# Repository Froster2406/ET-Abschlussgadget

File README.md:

# HS20-23 ET Abschlussgadget

Als Teil der Abschlusszeitung gibt es auch dieses Jahr wieder ein kleines Gadget kostenfrei dazu. Ganz im Namen des Überthemas "ET im PRENpunkt" mit der Anlehung an "Familien im Brennpunkt", kannst auch Du herausfinden, wie viel ET in Dir steckt. Aber nur wenn Du so asozial wie ein ET'ler bist, schaltet sich die geheime Zusatzfunktion frei.

## Verwendung

* Beiligende Batterie einlegen
* Schalter auf Platine in ON-Zustand versetzten
* Finger auf "Drück mich!" legen
* Anzeige ablesen

<details>
<summary>only for real engineers</summary>
<br>
You deem yourself a true engineer? Great!<br>
Tag along as we dive deeper into how you can reprogram the microcontroller. <br>

## general information
* [Reference Manual](https://ww1.microchip.com/downloads/aemDocuments/documents/MCU08/ProductDocuments/DataSheets/ATtiny212-214-412-414-416-DataSheet-DS40002287A.pdf)
* There are two pins (J1 & J2) on the side of the PCB than can be freely addressed, without interfering with the main functionality of the board

## preresquisites
* USB to serial converter | USB to TTL converter <br>
`Any converter (3.3V or 5V) off of Aliexpress, Ebay, Mouser, etc. will do.`
* 1kOhm resistor <br>
* Wires to connect the PCB to the converter <br>
* [Microchip Studio](https://www.microchip.com/en-us/tools-resources/develop/microchip-studio) <br>
* [Python](https://www.python.org/downloads/) installed on your machine <br>
* Python package: [pymcuprog](https://pypi.org/project/pymcuprog/) <br>
`pip install pymcuprog`<br>

## wiring diagram 
https://github.com/microchip-pic-avr-tools/pymcuprog#serial-port-updi-pyupdi

## reprogramming
* Connect the PCB to the USB to serial converter according to the wiring diagram
* Adjust the code to your liking and build it with F7
* Navigate to the python-programmer script <br>
`cd <YOUR_PATH>\ET-Abschlussgadget\Software\Programmer Python`
* Run the programming command <br>
`python attiny414.py <COM_PORT> <ABSOLUTE_PATH_TO_HEX_FILE_YOU_COMPILED_WITH_MICROCHIP_STUDIO>` <br>
*COM_PORT: If unknown, the available ones will be printed in the console*

* Power cycle the PCB

</details>

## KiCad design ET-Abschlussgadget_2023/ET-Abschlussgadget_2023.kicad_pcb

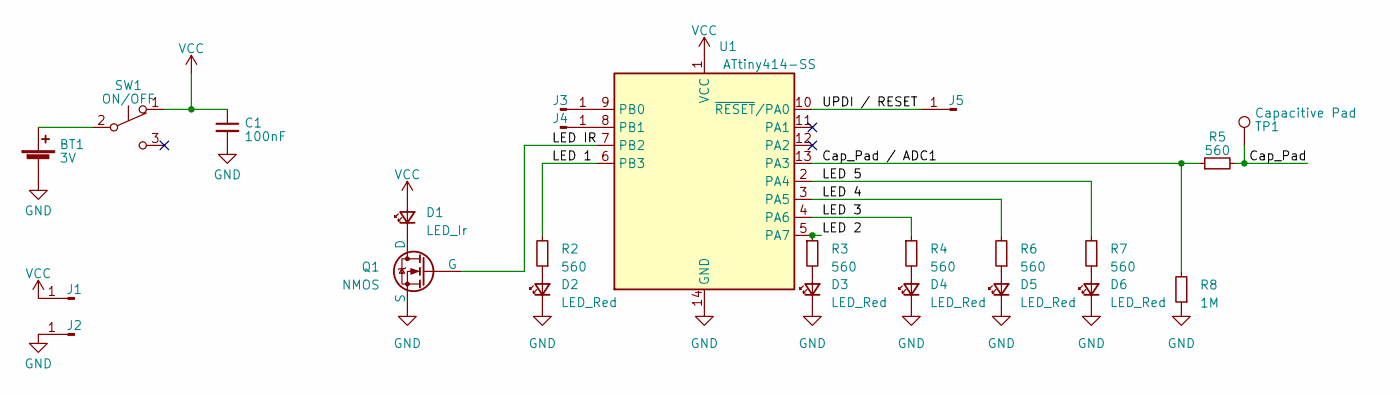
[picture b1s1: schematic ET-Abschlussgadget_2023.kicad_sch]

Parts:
BT1: 3V; BAT-SMD_CR2032-3V; LCSC C70373
C1: 100nF; C0603; LCSC C38141
D1: LED_Ir; XS-IR04A05-802; LCSC C396649
D2, D3, D4, D5, D6: LED_Red; LED0603-RD_RED; LCSC C965799
J1, J2: EXTCLK; TestPoint_Pad_D2.0mm
J3: PB0; TestPoint_Pad_D1.0mm
J4: PB1; TestPoint_Pad_D1.0mm
J5: UPDI / RESET; TestPoint_Pad_D2.0mm
Q1: NMOS; SOT-23-3_L2.9-W1.3-P1.90-LS2.4-BR
R2, R3, R4, R5, R6, R7: 560; R_0603_1608Metric_Pad0.98x0.95mm_HandSolder; LCSC C5140946
R8: 1M; R_0603_1608Metric_Pad0.98x0.95mm_HandSolder; LCSC C5140946
SW1: ON/OFF; SW-TH_MSK12C02; LCSC C2681568
TP1: Capacitive Pad; TestPoint_Pad_4.0x4.0mm
U1: ATtiny414-SS; SOIC-14_L8.7-W3.9-P1.27-LS6.0-BL; LCSC C189365

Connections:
/Cap_Pad: R5.2, TP1.1
/Cap_Pad / ADC1: R5.1, R8.2, U1.13 (PA3)
/LED 1: R2.2, U1.6 (PB3)
/LED 2: R3.1, U1.5 (PA7)
/LED 3: R4.1, U1.4 (PA6)
/LED 4: R6.2, U1.3 (PA5)
/LED 5: R7.2, U1.2 (PA4)
/LED IR: Q1.2 (G), U1.7 (PB2); also elsewhere on the board
/UPDI / RESET: J5.1, U1.10 (~RESET/PA0)
GND: BT1.2 (-), C1.2, D2.1 (K), D3.1 (K), D4.1 (K), D5.1 (K), D6.1 (K), J2.1, Q1.3 (S), R8.1, U1.14 (GND); also elsewhere on the board
unnamed: BT1.1 (+), SW1.2 (B)
unnamed 11: D1.1 (K), Q1.1 (D); also elsewhere on the board
unnamed: D2.2 (A), R2.1
unnamed: D3.2 (A), R3.2
unnamed: D4.2 (A), R4.2
unnamed: D5.2 (A), R6.1
unnamed: D6.2 (A), R7.1
unnamed: J3.1, U1.9 (PB0)
unnamed: J4.1, U1.8 (PB1)
VCC: C1.1, D1.2 (A), J1.1, SW1.1 (A), U1.1 (VCC)

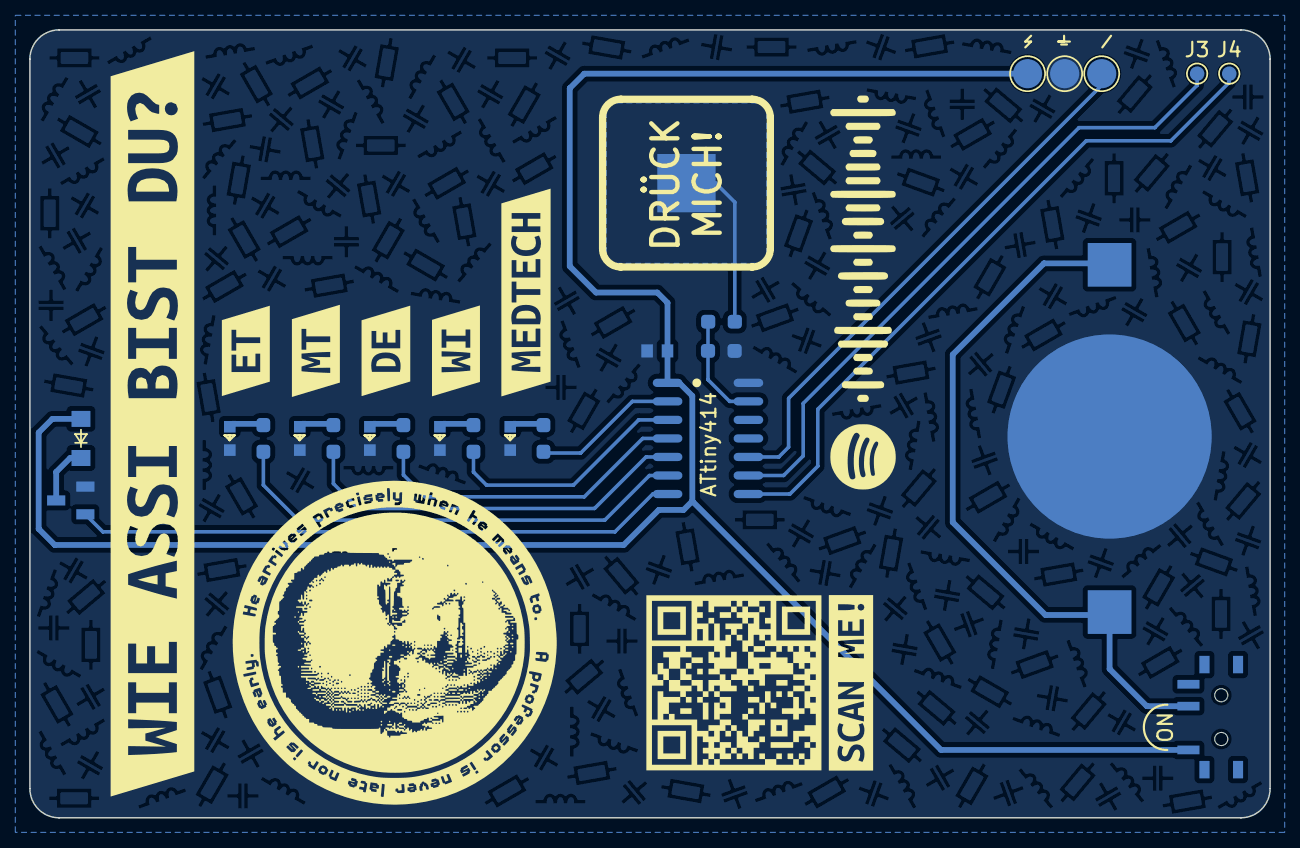
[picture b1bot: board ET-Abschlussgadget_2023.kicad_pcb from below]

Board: 2 copper layers, 85.0 x 54.0 mm, 31 parts (31 on the bottom side), 20 nets.

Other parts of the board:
Q2: SI2302_C2891732; SOT-23-3_L2.9-W1.3-P1.90-LS2.4-BR
kibuzzard-642F12C7: G***; kibuzzard-642F12C7
kibuzzard-642F12D5: G***; kibuzzard-642F12D5
kibuzzard-642F12E3: G***; kibuzzard-642F12E3
kibuzzard-642F12EF: G***; kibuzzard-642F12EF
kibuzzard-642F1274: G***; kibuzzard-642F1274
kibuzzard-642F1300: G***; kibuzzard-642F1300
kibuzzard-64480F6A: G***; kibuzzard-64480F6A

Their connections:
/LED IR: Q2.1 (G); also elsewhere on the board
GND: Q2.2 (S); also elsewhere on the board
unnamed 11: Q2.3 (D); also elsewhere on the board

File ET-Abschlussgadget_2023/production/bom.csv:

Designator,Footprint,Quantity,Value,LCSC Part #
BT1,BAT-SMD_CR2032-3V,1,3V,C70373
C1,C0603,1,100nF,C38141
D1,XS-IR04A05-802,1,LED_Ir,C396649
"D2, D3, D4, D5, D6",LED0603-RD_RED,5,LED_Red,C965799
"J1, J2",TestPoint_Pad_D2.0mm,2,EXTCLK,
J3,TestPoint_Pad_D1.0mm,1,PB0,
J4,TestPoint_Pad_D1.0mm,1,PB1,
J5,TestPoint_Pad_D2.0mm,1,UPDI / RESET,
Q2,SOT-23-3_L2.9-W1.3-P1.90-LS2.4-BR,1,SI2302_C2891732,C2891732
"R2, R3, R4, R5, R6, R7",0603,6,560,C5140946
R8,0603,1,1M,C5140946
SW1,SW-TH_MSK12C02,1,ON/OFF,C2681568
TP1,TestPoint_Pad_4.0x4.0mm,1,Capacitive Pad,
U1,SOIC-14_L8.7-W3.9-P1.27-LS6.0-BL,1,ATtiny414-SS,C189365

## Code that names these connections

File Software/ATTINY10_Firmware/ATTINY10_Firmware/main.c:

/*
                                         ATtiny10
                                 +----------------------+
        AIN0/ADC0/OC0A/PCINT0  --| 1 (PB0)  (PB3/RST) 6 |--  ADC3/PCINT3
                                 |                      |
                                 |                      |
                               --| 2 (GND)      (VCC) 5 |--
                                 |                      |
                                 |                      |
 AIN1/ADC1/OC0B/PCINT1/QTouch  --| 3 (PB1)      (PB2) 4 |--  ADC2/PCINT2
                                 +----------------------+

*/


#define F_CPU 8000000

#include <avr/io.h>
#include <util/delay.h>
#include "tiny_lib.h"
#include "TinyTouchLib.h"

uint8_t irCmd[] = {0x76, 0xB5, 0xAA, 0xB5, 0xAD};

int main(void)
{
	/*
	// Blink led on pin 1
	// -----------------------------
	// Pin 1 as output
    DDRB = 0b0001;
    // Toggle OC0A, CTC mode
	TCCR0A = 1<<COM0A0 | 0<<WGM00;
    // CTC mode; use OCR0A
	TCCR0B = 1<<WGM02 | 3<<CS00;
	// 1 second
	OCR0A = 15624;
	*/
	
	/*
	// IR led pwm signal
	// -----------------------------
	led6On();
	pwm1Init();
	pwm1On();
	_delay_us(560);
	pwm1Off();
	_delay_us(560);
	*/
	
	//tinytouch_init();
	
	/*
	DDRB = 1;                    // PB0 as an output
	TCCR0A = 1<<COM0A0;          // Toggle OC0A
	TCCR0B = 1<<WGM02 | 3<<CS00; // CTC mode and set prescaler to 64
	OCR0A = 3905;                // Frequency 2Hz
	while (1);
	*/
	
	
	CCP    = 0xD8;
	CLKMSR = 0x00;
	CCP    = 0xD8;
	CLKPSR = 0X00;
	
	/*
	DDRB = 0b1111;
	PUEB = 0b0000;
	PORTB = 0b0000;
	*/
	
	while (1) 
    {
		/*
		PORTB = 0b0001;
		_delay_ms(200);
		PORTB = 0b0100;
		_delay_ms(200);
		*/
		
		/*
		// Capacitive touch sensor
		// -----------------------------
		if (tinytouch_sense() == tt_push) {
			led1On();
			_delay_ms(200);
			ledsOff();
		}
		*/
		
		/*
		// Send ir command
		// -----------------------------
		for(uint8_t n = 0; n < 2; n++) {
			for (uint8_t i = 0; i < sizeof(irCmd)/sizeof(irCmd[0]); i++) {
				for (uint8_t j = 0; j < sizeof(irCmd[0]); j++) {
					if (irCmd[i] & (1 << (7 - j))) {
						led6On();
						_delay_us(625);
					}
					else {
						ledsOff();
						_delay_us(625);
					}
				}
			}
			_delay_ms(25);
		}
		*/
		
		#define DEL 100
		
		// Blink 6 charlieplexed leds
		// -----------------------------
		led1On();
		_delay_ms(DEL);
		led2On();
		_delay_ms(DEL);
		led3On();
		_delay_ms(DEL);
		led4On();
		_delay_ms(DEL);
		led5On();
		_delay_ms(DEL);
		led6On();
		_delay_ms(DEL);
    }
}

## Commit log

2023-03-31 V0.1
2023-03-31 Added front silk screen
2023-03-31 Add rounded corners
2023-03-31 Add kicad backup directory to gitignore
2023-04-01 Added first & last name
2023-04-06 Add schematic
2023-04-06 Add basic layout
2023-04-06 Add testpoints, bottom silkscreen, rothli
2023-04-06 Fix silkscreen and solder mask
2023-04-06 Improve component and silkscreen placement
2023-04-06 Improve silkscreen
2023-04-06 Add inverted banner
2023-04-07 Add series resistor to capacitive pad
2023-04-07 Add bypass capacitor
2023-04-07 Add rounded tracks
2023-04-07 Remove unnecessary things from board
2023-04-13 Adjusted for prototyping Add gerber files Add fabrication request
2023-04-13 minor fix
2023-04-14 Add copper to front, Improve sillkscreen
2023-04-14 Add qr code to silkscreen
2023-04-15 Add switch, Change qr to be smaller
2023-04-18 Add mcu firmware project
2023-04-19 Add attiny programmer python cli tool
2023-04-19 Add attiny programmer arduino
2023-04-20 Add touch lib, Optimize gpio funtions
2023-04-21 Add ir command transmission
2023-04-24 Add material-list, Adjust footprints, add first datasheets
2023-04-24 Redone whole layout based around new MCU, button and batteryholder-footprints are still placeholder tbd
2023-04-24 Backup
2023-04-25 Changed button-footprint, moved resistors & capacitors from 0805 to 0603, minor tweaks
2023-04-25 Improve back silkscreen and routing
2023-04-25 Add back copper pattern
2023-04-26 Updated switch & battery holder footprint, adjusted manual BOM
2023-04-26 Move switch, Move testpads, Add spotify code
2023-04-26 Improve attiny10 programming
2023-04-26 Improve back copper pattern
2023-04-27 Fix spotify code
2023-04-27 Generated Output-Files, Added LCSC-Partnumbers to schematic
2023-04-27 minor fixes
2023-04-27 updated materiallist
2023-04-27 Removed all designators, add silkscreen below MCU and LEDs
2023-04-28 Create attiny414 firmware project
2023-04-28 Replaced all footprints exept 0603-resistor with LCSC-footprints, generated new production-files, replaced 0805-cap with 0603-cap inside materialliste
2023-04-28 Add led functions
2023-04-28 First port of TinyTouchLib from Attiny10 to Attiny414
2023-04-28 Fix firmware project file
2023-04-28 Anleitung Gadget
2023-05-01 Add attiny414 programmer script
2023-05-02 Update TinyTouchLib, add code to main file, add debug code for PB0-pin
2023-05-05 updated pcbTest function, add tinytouch_init-function
2023-05-06 Add working ir command
2023-05-06 Update ir command to use hardware timer
2023-05-06 Add automatic programming on build
2023-05-06 Fix tinytouchlib
2023-05-07 removed clk-pad from pcb, increased size of rothli-sticker, change IR-diode resistor from 590 to 220
2023-05-07 Add serial debug output
2023-05-07 Add low pass filter, Update thresholds
2023-05-07 Add ground plane pattern to entire back side
2023-05-08 removed redundant data
2023-05-10 Updated schematic with MOSFET and pulldown resistors, changed footprint for IR-diode
2023-05-10 Remove pulldown, Update resistors, Update routing
2023-05-11 Replaced parts in materialliste, replaced some footprints, generade production-files with JLC-plugin
2023-05-11 Final export
2023-05-25 Move libraries to separate projects, Add test ptoject
2023-05-25 Move all ir functions to library
2023-05-27 Fix capacitive touch using wrong pin
2023-05-27 Add path for external libraries
2023-05-29 Fix ir command
2023-05-29 Add startup animation, Add measurement animation
2023-05-29 Add loop to python programmer
2023-06-01 Renamed hardware-folder; add correct datasheets; updated materialliste.xlsx
